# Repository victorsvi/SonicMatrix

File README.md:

# SonicMatrix
This projects implements hardware and software of a ultrasonic matrix for particle manipulation. The device is able of dinamically manipulating particles over a plane using only an ultrasonic phased array and a reflector.

The project is composed of a custom board with 64 ultrasonic transducers that are controled individually by a code that runs on a Arduino Mega.

The code is meant to be compiled and uploaded from the Arduino IDE.

You can find more information about what is a ultrasonic matrix and how it can manipulate particles in the file "Manipulação Acústica com Matriz Ultrassônica.pdf" (written in portuguese).

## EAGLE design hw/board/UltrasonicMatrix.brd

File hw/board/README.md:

# TRANSDUCER ARRAY BOARD

This custom pcb is used to hold the transducers and to amplify the microcontroller output.
The board was designed with Eagle.

it was designed to be etched at home with photoresist film, so there were some restrictions to the routing:
- The board can have a maximum of 2 layers (top and bottom)
- Vias are just a hole with a manually soldered jumper from top to bottom. They need to be the size of at least a trough hole component pad. For this reason, vias were used just for the power and ground rails.
- As vias can't be used for signals, the transducers will be placed and soldered from the top.
- 20mil is the limit for trace width and spacing between signals.

If you will etch with tonner transfer, the trace width might be too small.
If you will use a pcb manufacturing service, I advise to remake the design without the above restrictions. In this case, place the arduino and the power mosfets on one side and the transducers on the other side as it will be easier to replace some bad part. Also put series resistors between the arduino pin and the power mosfet input to protect the microcontroller in case the mosfet goes short.

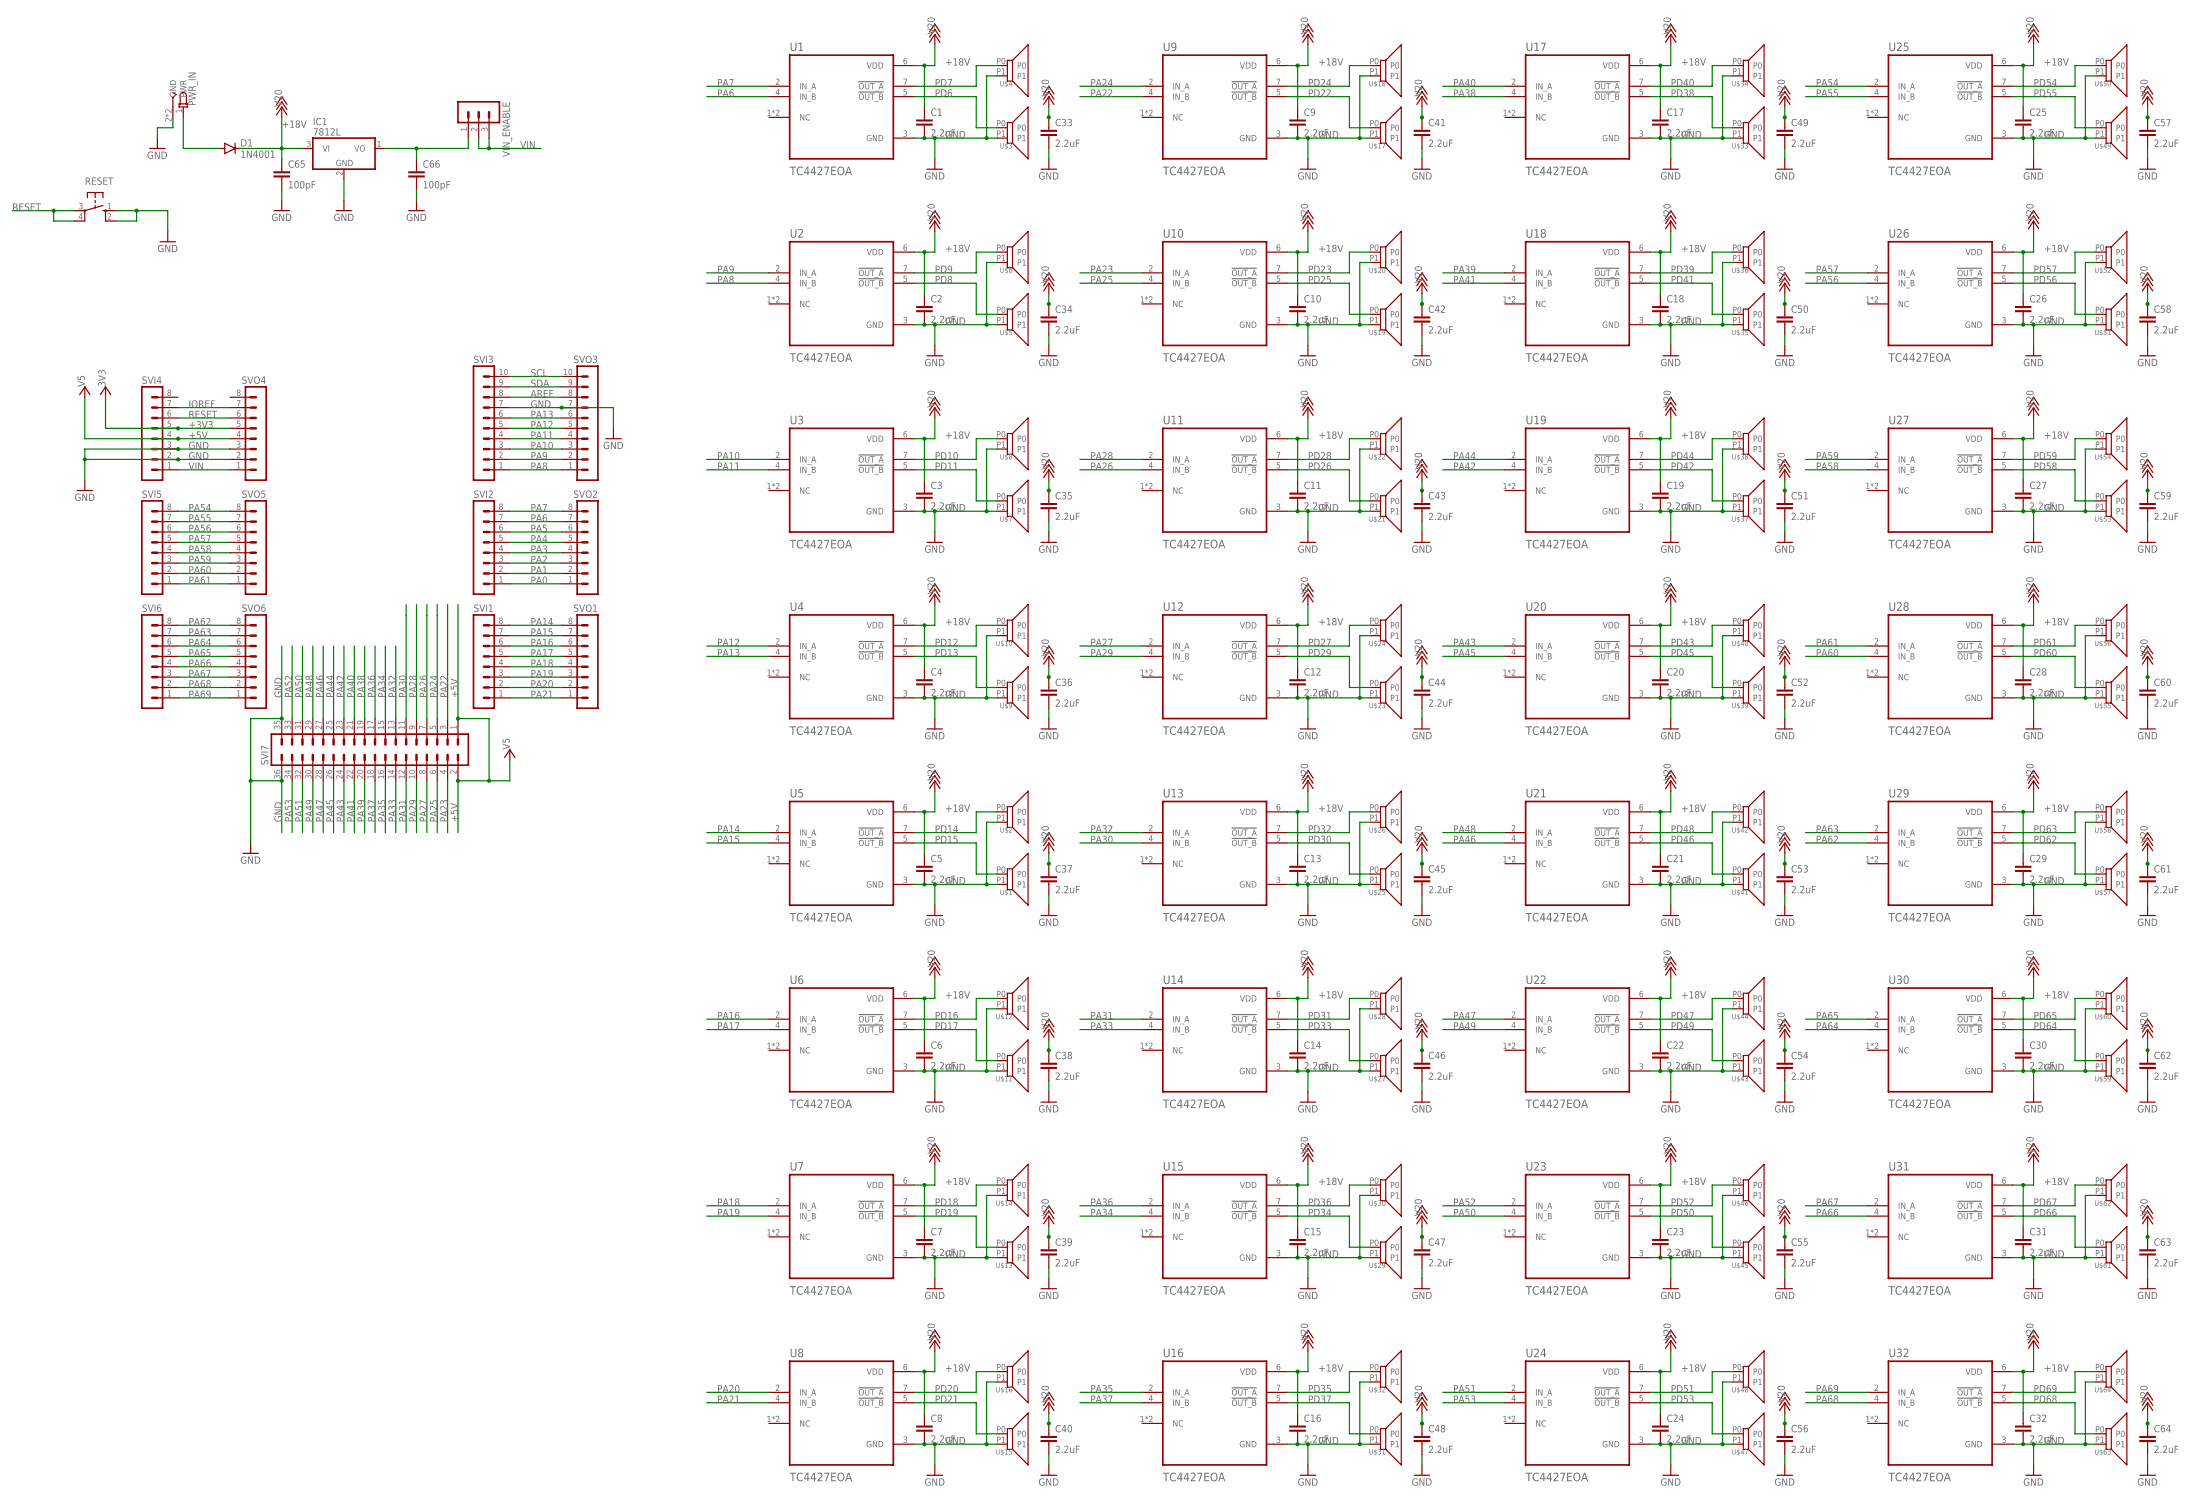
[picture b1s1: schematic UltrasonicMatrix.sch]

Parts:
C1, C2, C3, C4, C5, C6, C7, C8, C9, C10, C11, C12, C13, C14, C15, C16, C17, C18, C19, C20, C21, C22, C23, C24, C25, C26, C27, C28, C29, C30, C31, C32, C33, C34, C35, C36, C37, C38, C39, C40, C41, C42, C43, C44, C45, C46, C47, C48, C49, C50, C51, C52, C53, C54, C55, C56, C57, C58, C59, C60, C61, C62, C63, C64: 2.2uF; C1206
C65, C66: 100pF; C050-025X075
D1: 1N4001; DO41-10
IC1: 7812L; TO92
PWR_IN: DCJACK
RESET: 10-XX; B3F-10XX
SVI1, SVI2, SVI4, SVI5, SVI6: MA08-1
SVI3: MA10-1
SVI7: MA18-2
SVO1, SVO2, SVO4, SVO5, SVO6: MA08-1
SVO3: MA10-1
U1, U2, U3, U4, U5, U6, U7, U8, U9, U10, U11, U12, U13, U14, U15, U16, U17, U18, U19, U20, U21, U22, U23, U24, U25, U26, U27, U28, U29, U30, U31, U32: TC4427EOA; SOIC127P599X175-8N
U$1, U$2, U$3, U$4, U$5, U$6, U$7, U$8, U$9, U$10, U$11, U$12, U$13, U$14, U$15, U$16, U$17, U$18, U$19, U$20, U$21, U$22, U$23, U$24, U$25, U$26, U$27, U$28, U$29, U$30, U$31, U$32, U$33, U$34, U$35, U$36, U$37, U$38, U$39, U$40, U$41, U$42, U$43, U$44, U$45, U$46, U$47, U$48, U$49, U$50, U$51, U$52, U$53, U$54, U$55, U$56, U$57, U$58, U$59, U$60, U$61, U$62, U$63, U$64: TCT40-16
VIN_ENABLE: MA03-1

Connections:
+3V3: SVI4.5, SVO4.5
+5V: SVI4.4, SVI7.1, SVI7.2, SVO4.4
+18V: C1.1, C2.1, C3.1, C4.1, C5.1, C6.1, C7.1, C8.1, C9.1, C10.1, C11.1, C12.1, C13.1, C14.1, C15.1, C16.1, C17.1, C18.1, C19.1, C20.1, C21.1, C22.1, C23.1, C24.1, C25.1, C26.1, C27.1, C28.1, C29.1, C30.1, C31.1, C32.1, C33.1, C34.1, C35.1, C36.1, C37.1, C38.1, C39.1, C40.1, C41.1, C42.1, C43.1, C44.1, C45.1, C46.1, C47.1, C48.1, C49.1, C50.1, C51.1, C52.1, C53.1, C54.1, C55.1, C56.1, C57.1, C58.1, C59.1, C60.1, C61.1, C62.1, C63.1, C64.1, C65.1, D1.C, IC1.3 (VI), U1.6 (VDD), U2.6 (VDD), U3.6 (VDD), U4.6 (VDD), U5.6 (VDD), U6.6 (VDD), U7.6 (VDD), U8.6 (VDD), U9.6 (VDD), U10.6 (VDD), U11.6 (VDD), U12.6 (VDD), U13.6 (VDD), U14.6 (VDD), U15.6 (VDD), U16.6 (VDD), U17.6 (VDD), U18.6 (VDD), U19.6 (VDD), U20.6 (VDD), U21.6 (VDD), U22.6 (VDD), U23.6 (VDD), U24.6 (VDD), U25.6 (VDD), U26.6 (VDD), U27.6 (VDD), U28.6 (VDD), U29.6 (VDD), U30.6 (VDD), U31.6 (VDD), U32.6 (VDD)
AREF: SVI3.8, SVO3.8
GND: C1.2, C2.2, C3.2, C4.2, C5.2, C6.2, C7.2, C8.2, C9.2, C10.2, C11.2, C12.2, C13.2, C14.2, C15.2, C16.2, C17.2, C18.2, C19.2, C20.2, C21.2, C22.2, C23.2, C24.2, C25.2, C26.2, C27.2, C28.2, C29.2, C30.2, C31.2, C32.2, C33.2, C34.2, C35.2, C36.2, C37.2, C38.2, C39.2, C40.2, C41.2, C42.2, C43.2, C44.2, C45.2, C46.2, C47.2, C48.2, C49.2, C50.2, C51.2, C52.2, C53.2, C54.2, C55.2, C56.2, C57.2, C58.2, C59.2, C60.2, C61.2, C62.2, C63.2, C64.2, C65.2, C66.2, IC1.2 (GND), PWR_IN.2 (GND), PWR_IN.3 (GND), RESET.1 (S), RESET.2 (S1), SVI3.7, SVI4.2, SVI4.3, SVI7.35, SVI7.36, SVO3.7, SVO4.2, SVO4.3, U1.3 (GND), U2.3 (GND), U3.3 (GND), U4.3 (GND), U5.3 (GND), U6.3 (GND), U7.3 (GND), U8.3 (GND), U9.3 (GND), U10.3 (GND), U11.3 (GND), U12.3 (GND), U13.3 (GND), U14.3 (GND), U15.3 (GND), U16.3 (GND), U17.3 (GND), U18.3 (GND), U19.3 (GND), U20.3 (GND), U21.3 (GND), U22.3 (GND), U23.3 (GND), U24.3 (GND), U25.3 (GND), U26.3 (GND), U27.3 (GND), U28.3 (GND), U29.3 (GND), U30.3 (GND), U31.3 (GND), U32.3 (GND), U$1.P1, U$2.P1, U$3.P1, U$4.P1, U$5.P1, U$6.P1, U$7.P1, U$8.P1, U$9.P1, U$10.P1, U$11.P1, U$12.P1, U$13.P1, U$14.P1, U$15.P1, U$16.P1, U$17.P1, U$18.P1, U$19.P1, U$20.P1, U$21.P1, U$22.P1, U$23.P1, U$24.P1, U$25.P1, U$26.P1, U$27.P1, U$28.P1, U$29.P1, U$30.P1, U$31.P1, U$32.P1, U$33.P1, U$34.P1, U$35.P1, U$36.P1, U$37.P1, U$38.P1, U$39.P1, U$40.P1, U$41.P1, U$42.P1, U$43.P1, U$44.P1, U$45.P1, U$46.P1, U$47.P1, U$48.P1, U$49.P1, U$50.P1, U$51.P1, U$52.P1, U$53.P1, U$54.P1, U$55.P1, U$56.P1, U$57.P1, U$58.P1, U$59.P1, U$60.P1, U$61.P1, U$62.P1, U$63.P1, U$64.P1
IOREF: SVI4.7, SVO4.7
unnamed: D1.A, PWR_IN.1 (PWR)
unnamed: C66.1, IC1.1 (VO), VIN_ENABLE.1
PA0: SVI2.1, SVO2.1
PA1: SVI2.2, SVO2.2
PA2: SVI2.3, SVO2.3
PA3: SVI2.4, SVO2.4
PA4: SVI2.5, SVO2.5
PA5: SVI2.6, SVO2.6
PA6: SVI2.7, SVO2.7, U1.4 (IN_B)
PA7: SVI2.8, SVO2.8, U1.2 (IN_A)
PA8: SVI3.1, SVO3.1, U2.4 (IN_B)
PA9: SVI3.2, SVO3.2, U2.2 (IN_A)
PA10: SVI3.3, SVO3.3, U3.2 (IN_A)
PA11: SVI3.4, SVO3.4, U3.4 (IN_B)
PA12: SVI3.5, SVO3.5, U4.2 (IN_A)
PA13: SVI3.6, SVO3.6, U4.4 (IN_B)
PA14: SVI1.8, SVO1.8, U5.2 (IN_A)
PA15: SVI1.7, SVO1.7, U5.4 (IN_B)
PA16: SVI1.6, SVO1.6, U6.2 (IN_A)
PA17: SVI1.5, SVO1.5, U6.4 (IN_B)
PA18: SVI1.4, SVO1.4, U7.2 (IN_A)
PA19: SVI1.3, SVO1.3, U7.4 (IN_B)
PA20: SVI1.2, SVO1.2, U8.2 (IN_A)
PA21: SVI1.1, SVO1.1, U8.4 (IN_B)
PA22: SVI7.3, U9.4 (IN_B)
PA23: SVI7.4, U10.2 (IN_A)
PA24: SVI7.5, U9.2 (IN_A)
PA25: SVI7.6, U10.4 (IN_B)
PA26: SVI7.7, U11.4 (IN_B)
PA27: SVI7.8, U12.2 (IN_A)
PA28: SVI7.9, U11.2 (IN_A)
PA29: SVI7.10, U12.4 (IN_B)
PA30: SVI7.11, U13.4 (IN_B)
PA31: SVI7.12, U14.2 (IN_A)
PA32: SVI7.13, U13.2 (IN_A)
PA33: SVI7.14, U14.4 (IN_B)
PA34: SVI7.15, U15.4 (IN_B)
PA35: SVI7.16, U16.2 (IN_A)
PA36: SVI7.17, U15.2 (IN_A)
PA37: SVI7.18, U16.4 (IN_B)
PA38: SVI7.19, U17.4 (IN_B)
PA39: SVI7.20, U18.2 (IN_A)
PA40: SVI7.21, U17.2 (IN_A)
PA41: SVI7.22, U18.4 (IN_B)
PA42: SVI7.23, U19.4 (IN_B)
PA43: SVI7.24, U20.2 (IN_A)
PA44: SVI7.25, U19.2 (IN_A)
PA45: SVI7.26, U20.4 (IN_B)
PA46: SVI7.27, U21.4 (IN_B)
PA47: SVI7.28, U22.2 (IN_A)
PA48: SVI7.29, U21.2 (IN_A)
PA49: SVI7.30, U22.4 (IN_B)
PA50: SVI7.31, U23.4 (IN_B)
PA51: SVI7.32, U24.2 (IN_A)
PA52: SVI7.33, U23.2 (IN_A)
PA53: SVI7.34, U24.4 (IN_B)
PA54: SVI5.8, SVO5.8, U25.2 (IN_A)
PA55: SVI5.7, SVO5.7, U25.4 (IN_B)
PA56: SVI5.6, SVO5.6, U26.4 (IN_B)
PA57: SVI5.5, SVO5.5, U26.2 (IN_A)
PA58: SVI5.4, SVO5.4, U27.4 (IN_B)
PA59: SVI5.3, SVO5.3, U27.2 (IN_A)
PA60: SVI5.2, SVO5.2, U28.4 (IN_B)
PA61: SVI5.1, SVO5.1, U28.2 (IN_A)
PA62: SVI6.8, SVO6.8, U29.4 (IN_B)
PA63: SVI6.7, SVO6.7, U29.2 (IN_A)
PA64: SVI6.6, SVO6.6, U30.4 (IN_B)
PA65: SVI6.5, SVO6.5, U30.2 (IN_A)
PA66: SVI6.4, SVO6.4, U31.4 (IN_B)
PA67: SVI6.3, SVO6.3, U31.2 (IN_A)
PA68: SVI6.2, SVO6.2, U32.4 (IN_B)
PA69: SVI6.1, SVO6.1, U32.2 (IN_A)
PD6: U1.5 (!OUT_B), U$3.P0
PD7: U1.7 (!OUT_A), U$4.P0
PD8: U2.5 (!OUT_B), U$5.P0
PD9: U2.7 (!OUT_A), U$6.P0
PD10: U3.7 (!OUT_A), U$8.P0
PD11: U3.5 (!OUT_B), U$7.P0
PD12: U4.7 (!OUT_A), U$10.P0
PD13: U4.5 (!OUT_B), U$9.P0
PD14: U5.7 (!OUT_A), U$2.P0
PD15: U5.5 (!OUT_B), U$1.P0
PD16: U6.7 (!OUT_A), U$12.P0
PD17: U6.5 (!OUT_B), U$11.P0
PD18: U7.7 (!OUT_A), U$14.P0
PD19: U7.5 (!OUT_B), U$13.P0
PD20: U8.7 (!OUT_A), U$16.P0
PD21: U8.5 (!OUT_B), U$15.P0
PD22: U9.5 (!OUT_B), U$17.P0
PD23: U10.7 (!OUT_A), U$20.P0
PD24: U9.7 (!OUT_A), U$18.P0
PD25: U10.5 (!OUT_B), U$19.P0
PD26: U11.5 (!OUT_B), U$21.P0
PD27: U12.7 (!OUT_A), U$24.P0
PD28: U11.7 (!OUT_A), U$22.P0
PD29: U12.5 (!OUT_B), U$23.P0
PD30: U13.5 (!OUT_B), U$25.P0
PD31: U14.7 (!OUT_A), U$28.P0
PD32: U13.7 (!OUT_A), U$26.P0
PD33: U14.5 (!OUT_B), U$27.P0
PD34: U15.5 (!OUT_B), U$29.P0
PD35: U16.7 (!OUT_A), U$32.P0
PD36: U15.7 (!OUT_A), U$30.P0
PD37: U16.5 (!OUT_B), U$31.P0
PD38: U17.5 (!OUT_B), U$33.P0
PD39: U18.7 (!OUT_A), U$36.P0
PD40: U17.7 (!OUT_A), U$34.P0
PD41: U18.5 (!OUT_B), U$35.P0
PD42: U19.5 (!OUT_B), U$37.P0
PD43: U20.7 (!OUT_A), U$40.P0
PD44: U19.7 (!OUT_A), U$38.P0
PD45: U20.5 (!OUT_B), U$39.P0
PD46: U21.5 (!OUT_B), U$41.P0
PD47: U22.7 (!OUT_A), U$44.P0
PD48: U21.7 (!OUT_A), U$42.P0
PD49: U22.5 (!OUT_B), U$43.P0
PD50: U23.5 (!OUT_B), U$45.P0
PD51: U24.7 (!OUT_A), U$48.P0
PD52: U23.7 (!OUT_A), U$46.P0
PD53: U24.5 (!OUT_B), U$47.P0
PD54: U25.7 (!OUT_A), U$50.P0
PD55: U25.5 (!OUT_B), U$49.P0
PD56: U26.5 (!OUT_B), U$51.P0
PD57: U26.7 (!OUT_A), U$52.P0
PD58: U27.5 (!OUT_B), U$53.P0
PD59: U27.7 (!OUT_A), U$54.P0
PD60: U28.5 (!OUT_B), U$55.P0
PD61: U28.7 (!OUT_A), U$56.P0
PD62: U29.5 (!OUT_B), U$57.P0
PD63: U29.7 (!OUT_A), U$58.P0
PD64: U30.5 (!OUT_B), U$59.P0
PD65: U30.7 (!OUT_A), U$60.P0
PD66: U31.5 (!OUT_B), U$61.P0
PD67: U31.7 (!OUT_A), U$62.P0
PD68: U32.5 (!OUT_B), U$63.P0
PD69: U32.7 (!OUT_A), U$64.P0
RESET: RESET.3, RESET.4 (P1), SVI4.6, SVO4.6
SCL: SVI3.10, SVO3.10
SDA: SVI3.9, SVO3.9
VIN: SVI4.1, SVO4.1, VIN_ENABLE.2, VIN_ENABLE.3

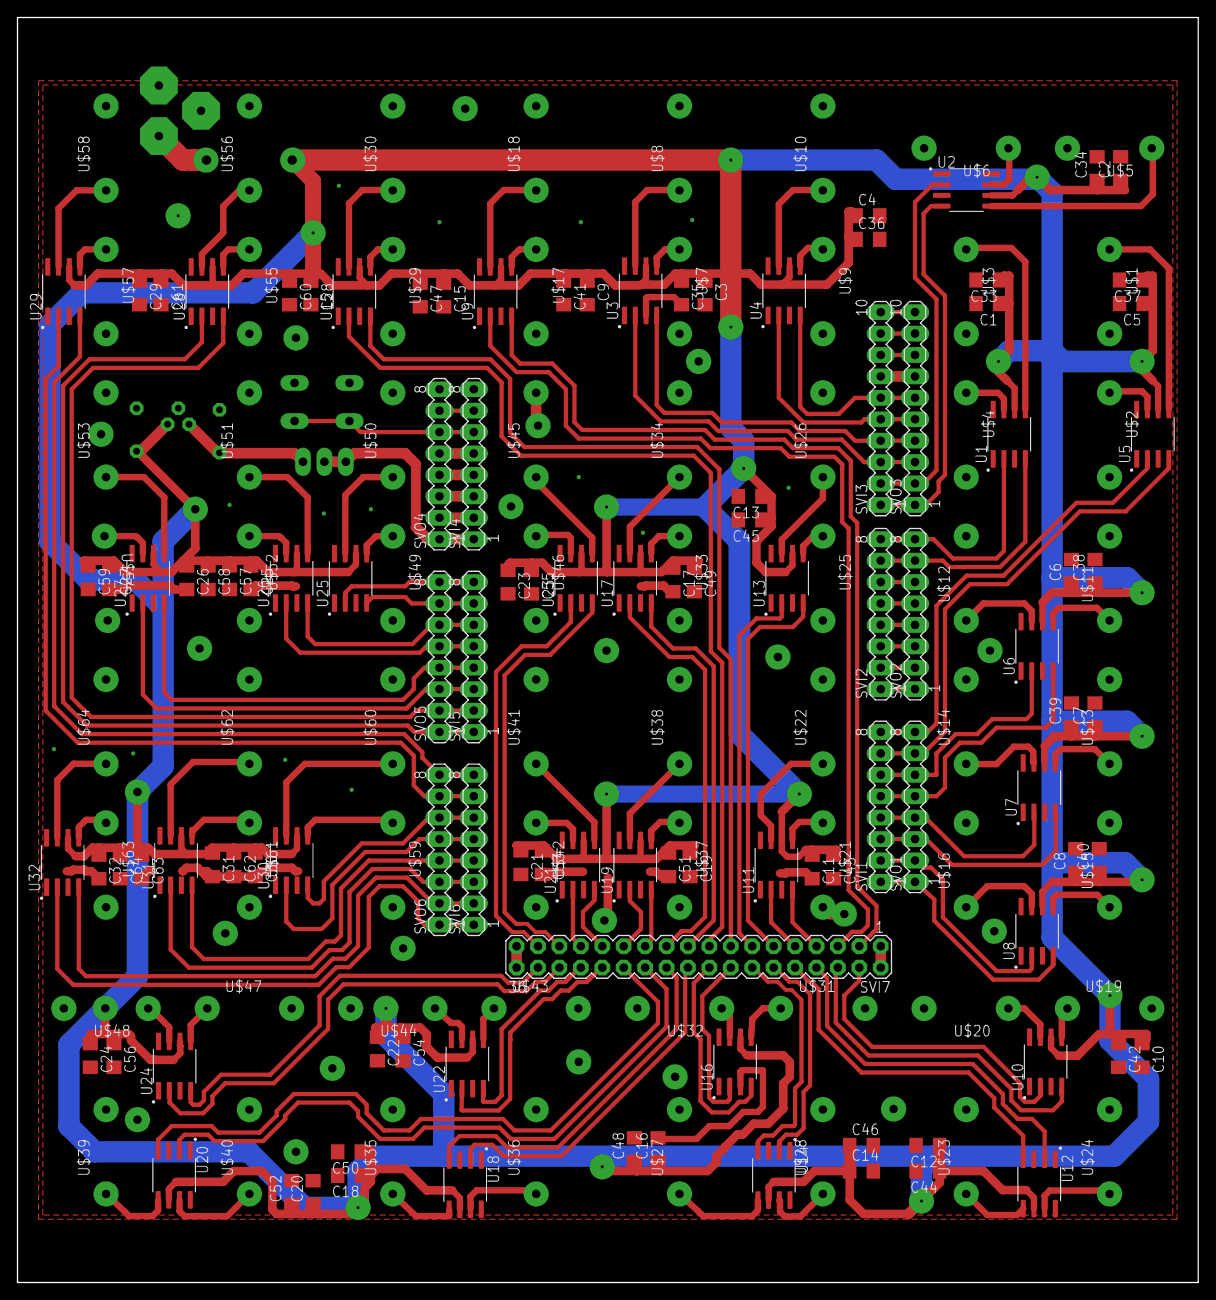
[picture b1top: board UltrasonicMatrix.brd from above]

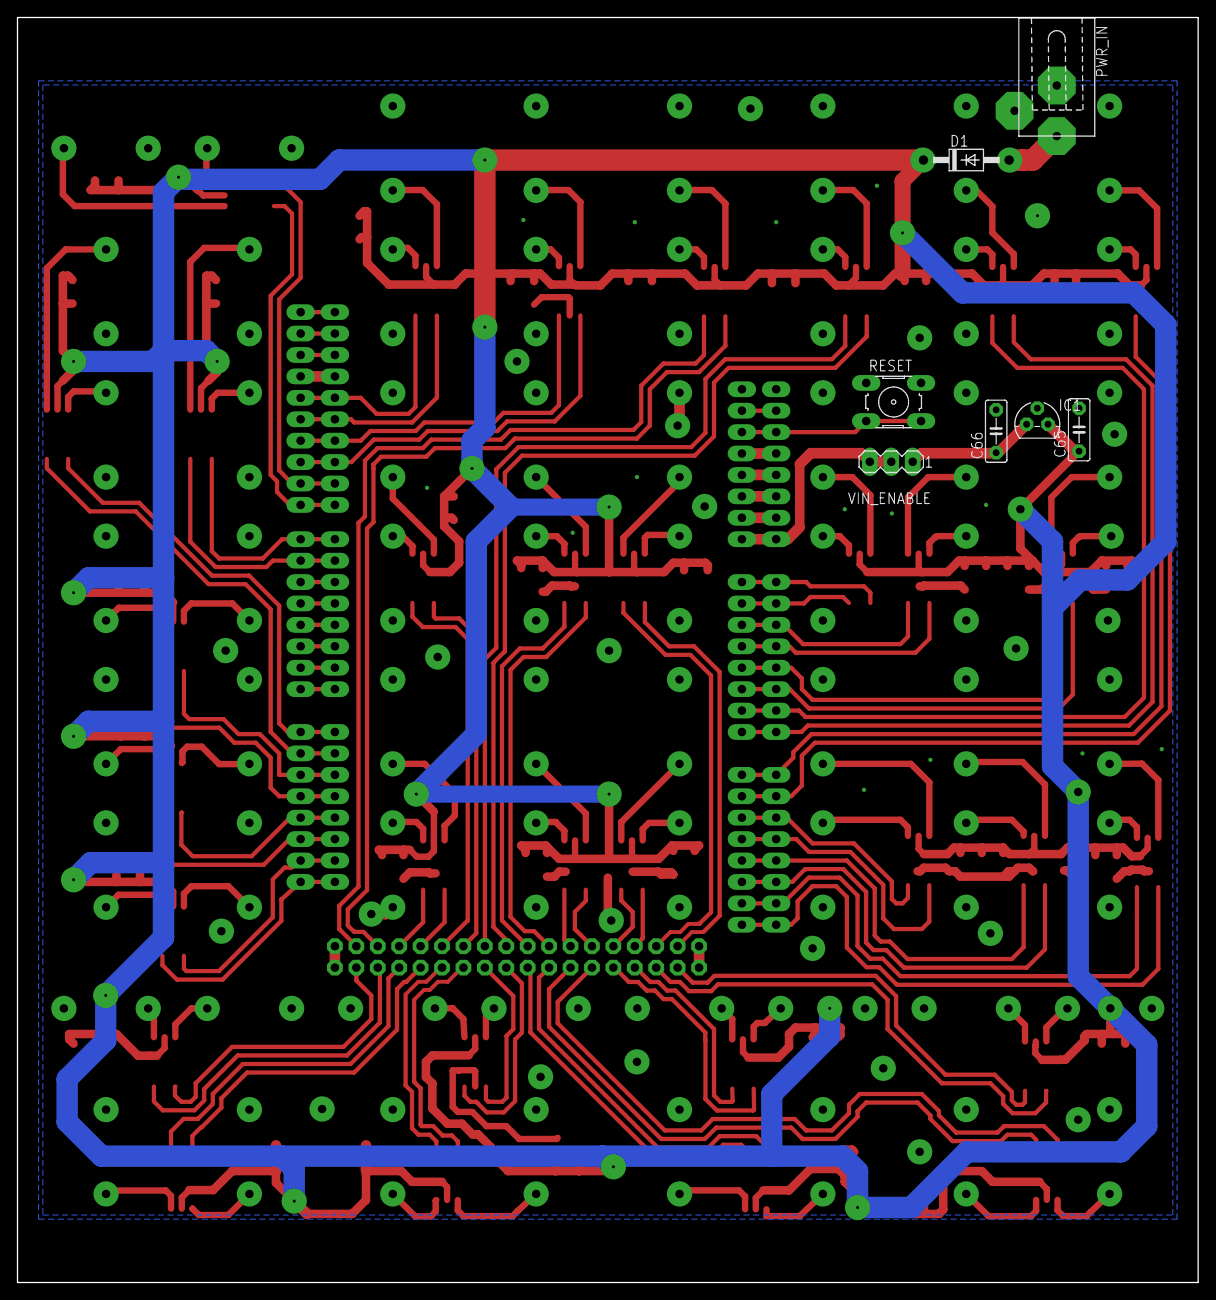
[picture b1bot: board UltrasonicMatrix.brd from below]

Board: 2 copper layers, 140.0 x 150.0 mm, 180 parts (7 on the bottom side), 146 nets.

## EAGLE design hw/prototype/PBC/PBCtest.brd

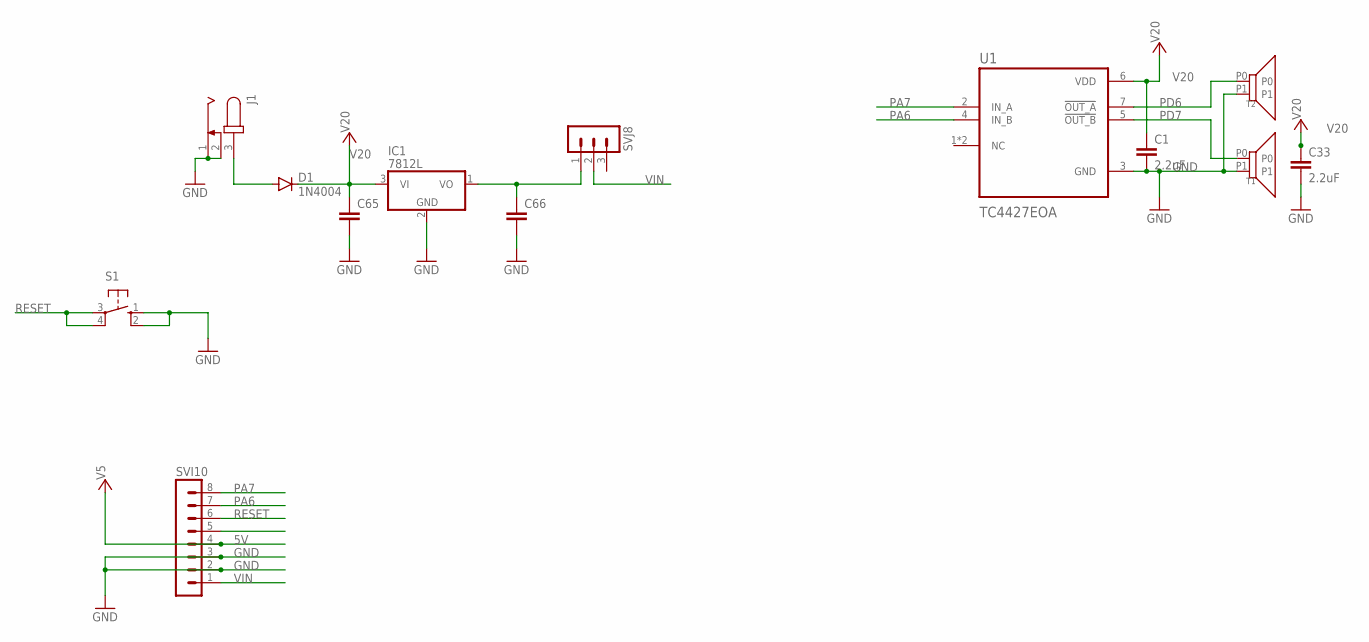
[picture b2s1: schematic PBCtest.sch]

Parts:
C1, C33: 2.2uF; C1206
C65, C66: C-EU050-025X075; C050-025X075
D1: 1N4004; DO41-10
IC1: 7812L; TO92
J1: JACK-PLUG0; SPC4077
S1: 10-XX; B3F-10XX
SVI10: MA08-1
SVJ8: MA03-1
T1, T2: TCT40-16
U1: TC4427EOA; SOIC127P599X175-8N

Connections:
5V: SVI10.4
GND: C1.2, C33.2, C65.2, C66.2, IC1.2 (GND), J1.1, J1.2, S1.1 (S), S1.2 (S1), SVI10.2, SVI10.3, T1.P1, T2.P1, U1.3 (GND)
unnamed: D1.A, J1.3
unnamed: C66.1, IC1.1 (VO), SVJ8.1
PA6: SVI10.7, U1.4 (IN_B)
PA7: SVI10.8, U1.2 (IN_A)
PD6: T2.P0, U1.7 (!OUT_A)
PD7: T1.P0, U1.5 (!OUT_B)
RESET: S1.3, S1.4 (P1), SVI10.6
V20: C1.1, C33.1, C65.1, D1.C, IC1.3 (VI), U1.6 (VDD)
VIN: SVI10.1, SVJ8.2

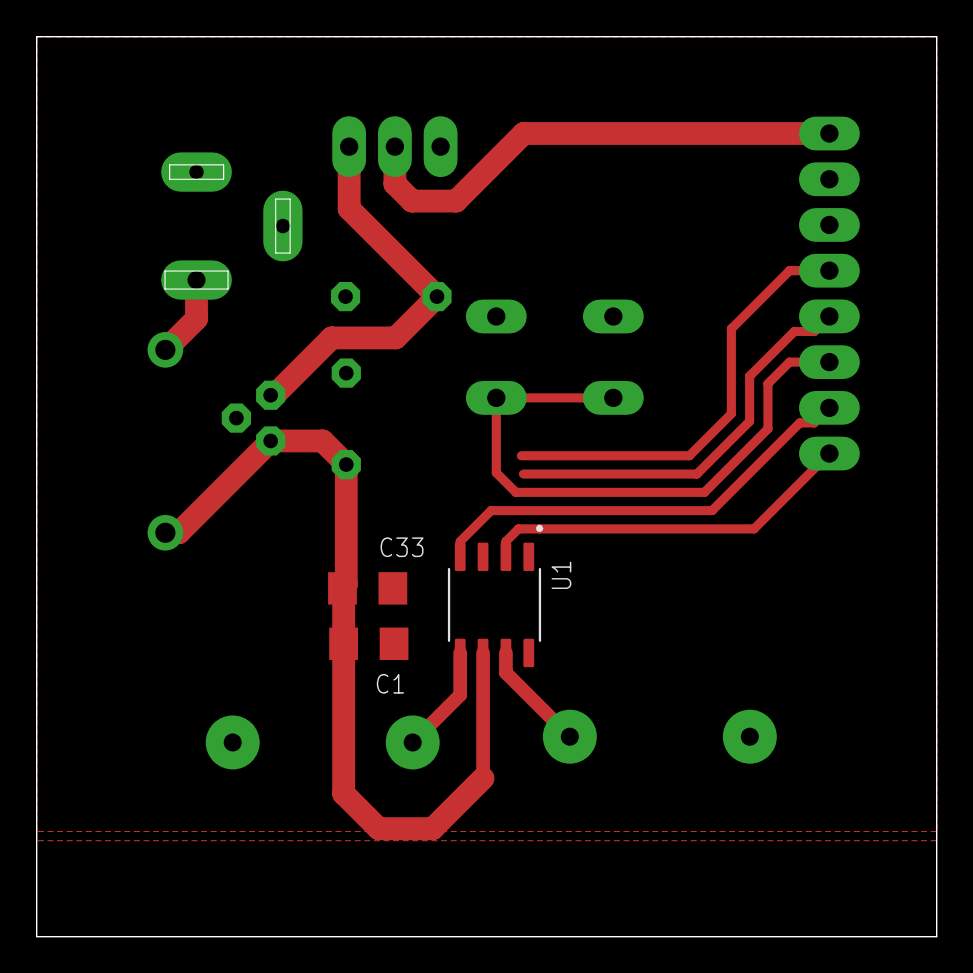
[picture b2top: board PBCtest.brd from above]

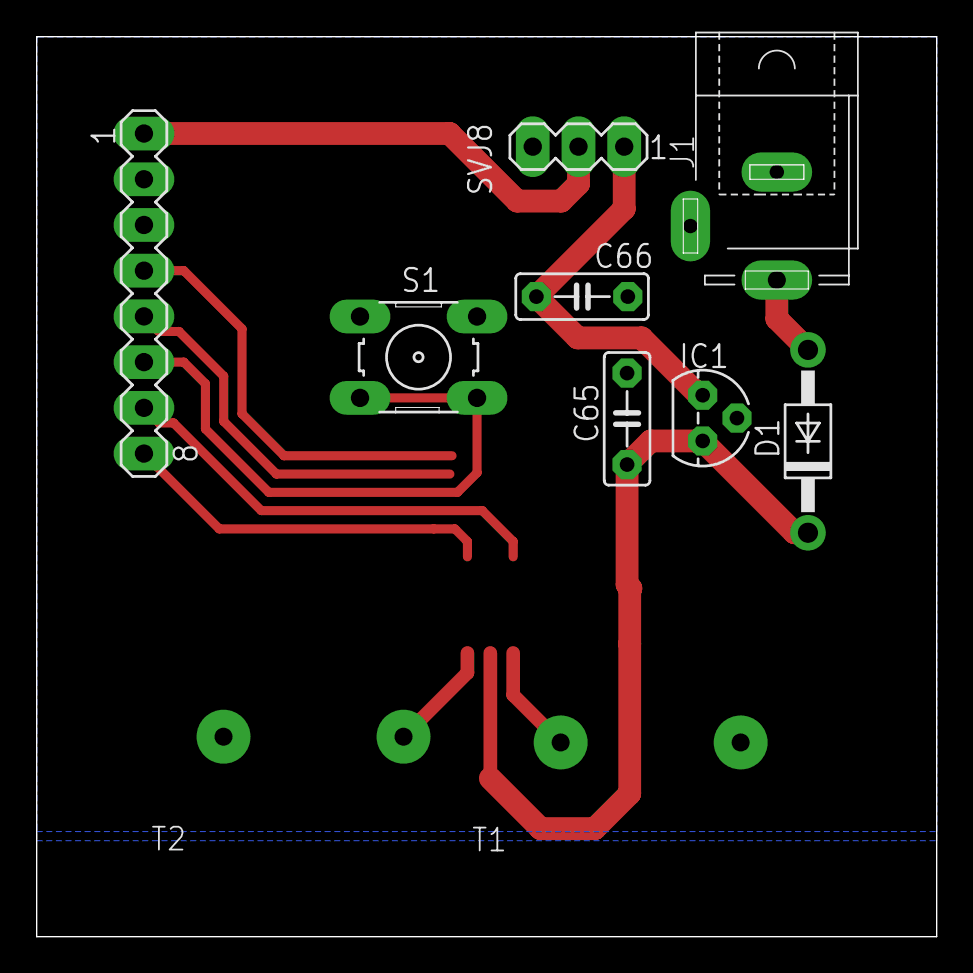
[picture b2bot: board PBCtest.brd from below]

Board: 2 copper layers, 50.0 x 50.0 mm, 13 parts (10 on the bottom side), 10 nets.

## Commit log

2020-03-02 Frist Comit
2020-03-03 Ultrasonic header
    the ultrassonic array data structures and interfaces were defined
2020-03-04 some funcions implemented
2020-03-12 Pattern generation
2020-03-14 Phase calculation and Dump funcion
2020-03-15 Ultrasonic test routine
    and bug fixes of Ultrasonic class
2020-03-16 Final test of Ultrasonic
    Bug fixes in phase and pattern calculation (rounding problems of integer algebra).
    Upgraded algorithm to generate the pattern.
    Updated test program.
    New csv export.
2020-03-17 Updated documentation
2020-03-17 Gave up optimization
2020-03-17 New stripped down version
    Also a fix on Ultrasonic:transd_calcflat which phase compensation were ignored
2020-03-19 Deception
    array_calc_focus is too slow :c
2020-03-20 Wont make a generic class :C
2020-03-22 Timer and serial input
2020-03-25 Pattern to Port
    VERY low performance. Will need to calculate the port registers for each "step" of the wave before outputing the signal
2020-03-30 Signal generation upgrade
2020-03-31 Trajectory planning
    + code organized
    - unused stuff
    + many misnamed variables fixed
2020-04-01 New timer
2020-04-02 Upgraded trajectory generation
2020-04-03 Calculate indexed axys speed
2020-04-16 Fix compilation problems
    no missing commas BUT extra commas :(
2020-05-09 Analyse Upgrades
2020-05-13 IT COMPILES!
2020-05-13 new debug features
2020-05-13 debug feature
2020-05-14 finished debug routines
2020-05-15 bug fixes
2020-05-16 More bug fixes
    Looks like Timer 4 and Timer 5 doesn't like each other, as theys weren't working at the same time. Changing from timer 5 to timer 3 solved the problem
2020-05-16 Documenting
    upgraded documentation of the files and funcions
2020-05-19 Documentation completed
    One function was moved from main.c to math.c as it doen't use any variable from main
2020-05-20 New folders for hardware development
2020-05-21 Created schematic
2020-05-22 schematic done
2020-05-23 tracing
2020-05-24 more tracing
2020-05-25 almost done
2020-05-26 more on board layout
2020-05-26 routing completed
2020-05-27 Board completed
2020-05-31 Board design enhancments
    * New alignment marks
    * Increased thermal isolation to 20mil
    * Upgraded PCBtest to new design rules with 20mil clearance and increased text size to test the same object sizes of the main board
2020-06-03 Updated test board
2020-06-04 Speed fix
    Optimized the signal output code. Now it takes 49 processor cycles to update the output
2020-06-05 Bit Banging
    * The Timer4 approach was replaced by a asm routine to archive a fast update rate.
    * The phase resolution was reduced to 8bits (wasn't able to reach 400kHz refresh rate).
    * Transducer spacing reduced to 1mm.
    * Fixed the duty cycle calculation in the pattern generation function.
2020-06-12 Board minor adjustments
    * Fixed some details in the board layout
    * Assigned the pin mapping in software
2020-06-14 Loaded Phase Compensation
2020-06-14 New debug mode
2020-06-16 Phase accuracy increased
    * Increased phase accuracy in focus calculations (Ultrasonic.c).
    * When calculating the pattern, will round the phase delay based on the phase resolution (Ultrasonic.c).
    * Solved the problem caused by the Timer0 interrupts. Now the Timer0 will be disabled until there is input data, when it will be enabled then disabled before activating the transducers.
    * Solved a problem in the calculation for the timer interval of the trajectory, which was caused if the speed was negative.
    * Fixed the pattern debug output, the pattern were being printed horizontally mirrored.
    * Created a layer for a millimeter grid in the board schematic.
2020-06-17 Fixed phase focusing bug
    * The software was calculating whats the phase that the wave would arrive at focal point and assuming this phase as phase delay. But it needed to complement that calculated phase to assume as phase d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
2020-06-22 New grid ruller
    new grid ruller with 0.5mm resolution
2020-06-30 article
2020-07-07 Removed backup files
2021-04-20 Improved documentation
2021-04-27 Organized files
    - Organized file structure
    - Unused files deleted
    - Updated project readme and added project cover
    - Created readme files
    - Added bill of materials
